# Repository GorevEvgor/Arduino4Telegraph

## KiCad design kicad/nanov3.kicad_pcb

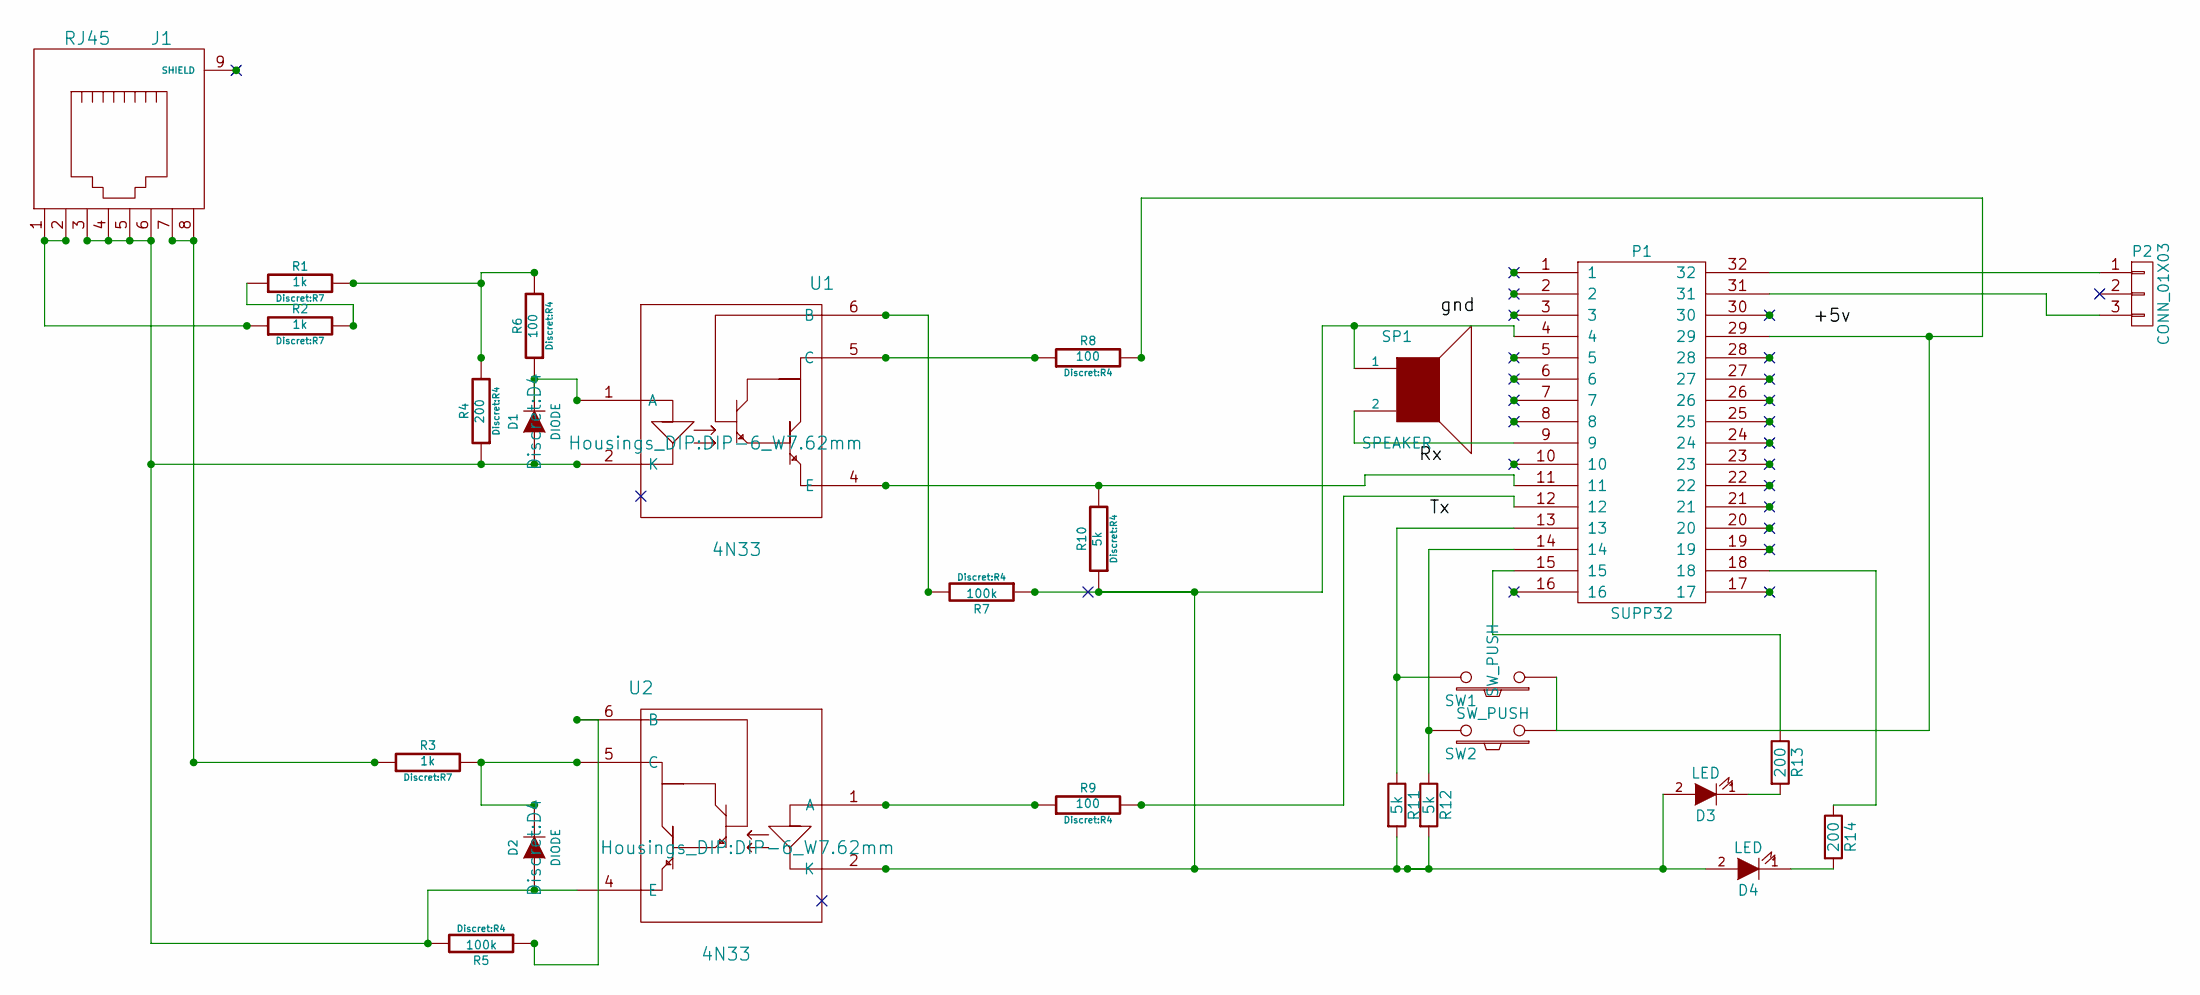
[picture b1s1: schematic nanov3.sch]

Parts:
D1, D2: DIODE; D4
D3, D4: LED; LED-5MM
J1: RJ45; RJ45_8
P1: SUPP32; DIP-32_W15.24mm
P2: CONN_01X03; Wafer_Horizontal10x5.8x7RM2.5-3
R1, R2, R3: 1k; R7
R4, R13, R14: 200; R4
R5, R7: 100k; R4
R6, R8, R9: 100; R4
R10, R11, R12: 5k; R4
SP1: SPEAKER; BUZZER
SW1, SW2: SW_PUSH; SW_Tactile_SPST_Angled
U1, U2: 4N33; DIP-6_W7.62mm

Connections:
unnamed: D1.1 (A), D2.1 (A), J1.3, J1.4, J1.5, J1.6, R4.1, R5.2, U1.2 (K), U2.4 (E)
unnamed: D1.2 (K), R6.1, U1.1 (A)
unnamed: D2.2 (K), R3.2, U2.5 (C)
unnamed: D3.1 (K), R13.2
unnamed: D3.2 (A), D4.2 (A), P1.4, R7.1, R10.1, R11.2, R12.2, SP1.1, U2.2 (K)
unnamed: D4.1 (K), R14.2
unnamed: J1.1, J1.2, R2.1
unnamed: J1.7, J1.8, R3.1
unnamed: P1.9, SP1.2
unnamed: P1.11, R10.2, U1.4 (E)
unnamed: P1.12, R9.2
unnamed: P1.13, R11.1, SW1.2
unnamed: P1.14, R12.1, SW2.2
unnamed: P1.15, R13.1
unnamed: P1.18, R14.1
unnamed: P1.29, R8.2, SW1.1, SW2.1
unnamed: P1.31, P2.3
unnamed: P1.32, P2.1
unnamed: R1.1, R2.2
unnamed: R1.2, R4.2, R6.2
unnamed: R5.1, U2.6 (B)
unnamed: R7.2, U1.6 (B)
unnamed: R8.1, U1.5 (C)
unnamed: R9.1, U2.1 (A)

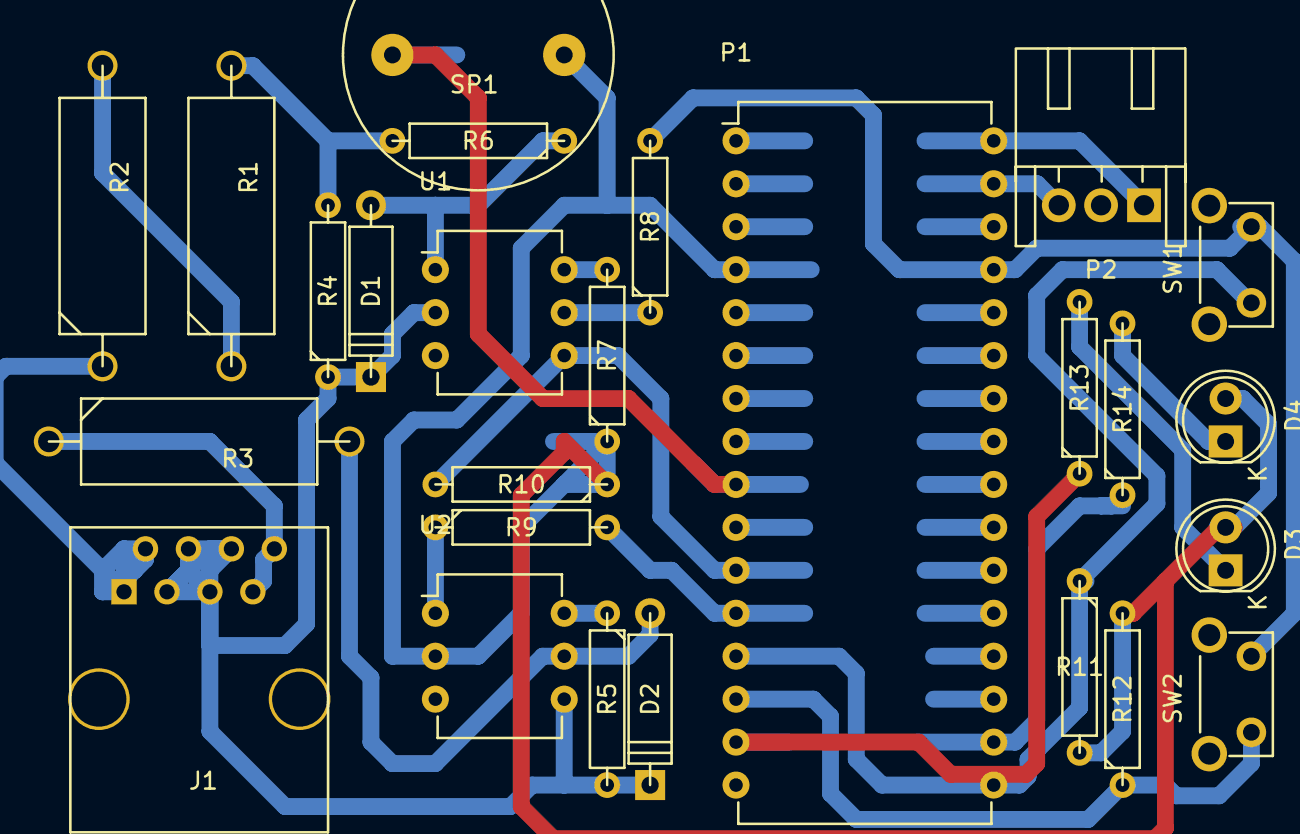
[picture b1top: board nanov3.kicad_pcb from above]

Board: 2 copper layers, 26 parts (0 on the bottom side), 24 nets.

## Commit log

2016-05-20 начало
2016-05-20 плата
2016-05-20 рабочий вариант с очередью кнопкой и бипером
2016-05-20 новая плата
2016-05-20 с печатью
2017-08-25 Добавлена поддержка utf-8 двухкнопочная версия с включенным автоответом работа с altsoftseral 1.4
